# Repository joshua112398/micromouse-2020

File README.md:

# micromouse-2020

Board and schematic files for use on EAGLE or other compatible software.

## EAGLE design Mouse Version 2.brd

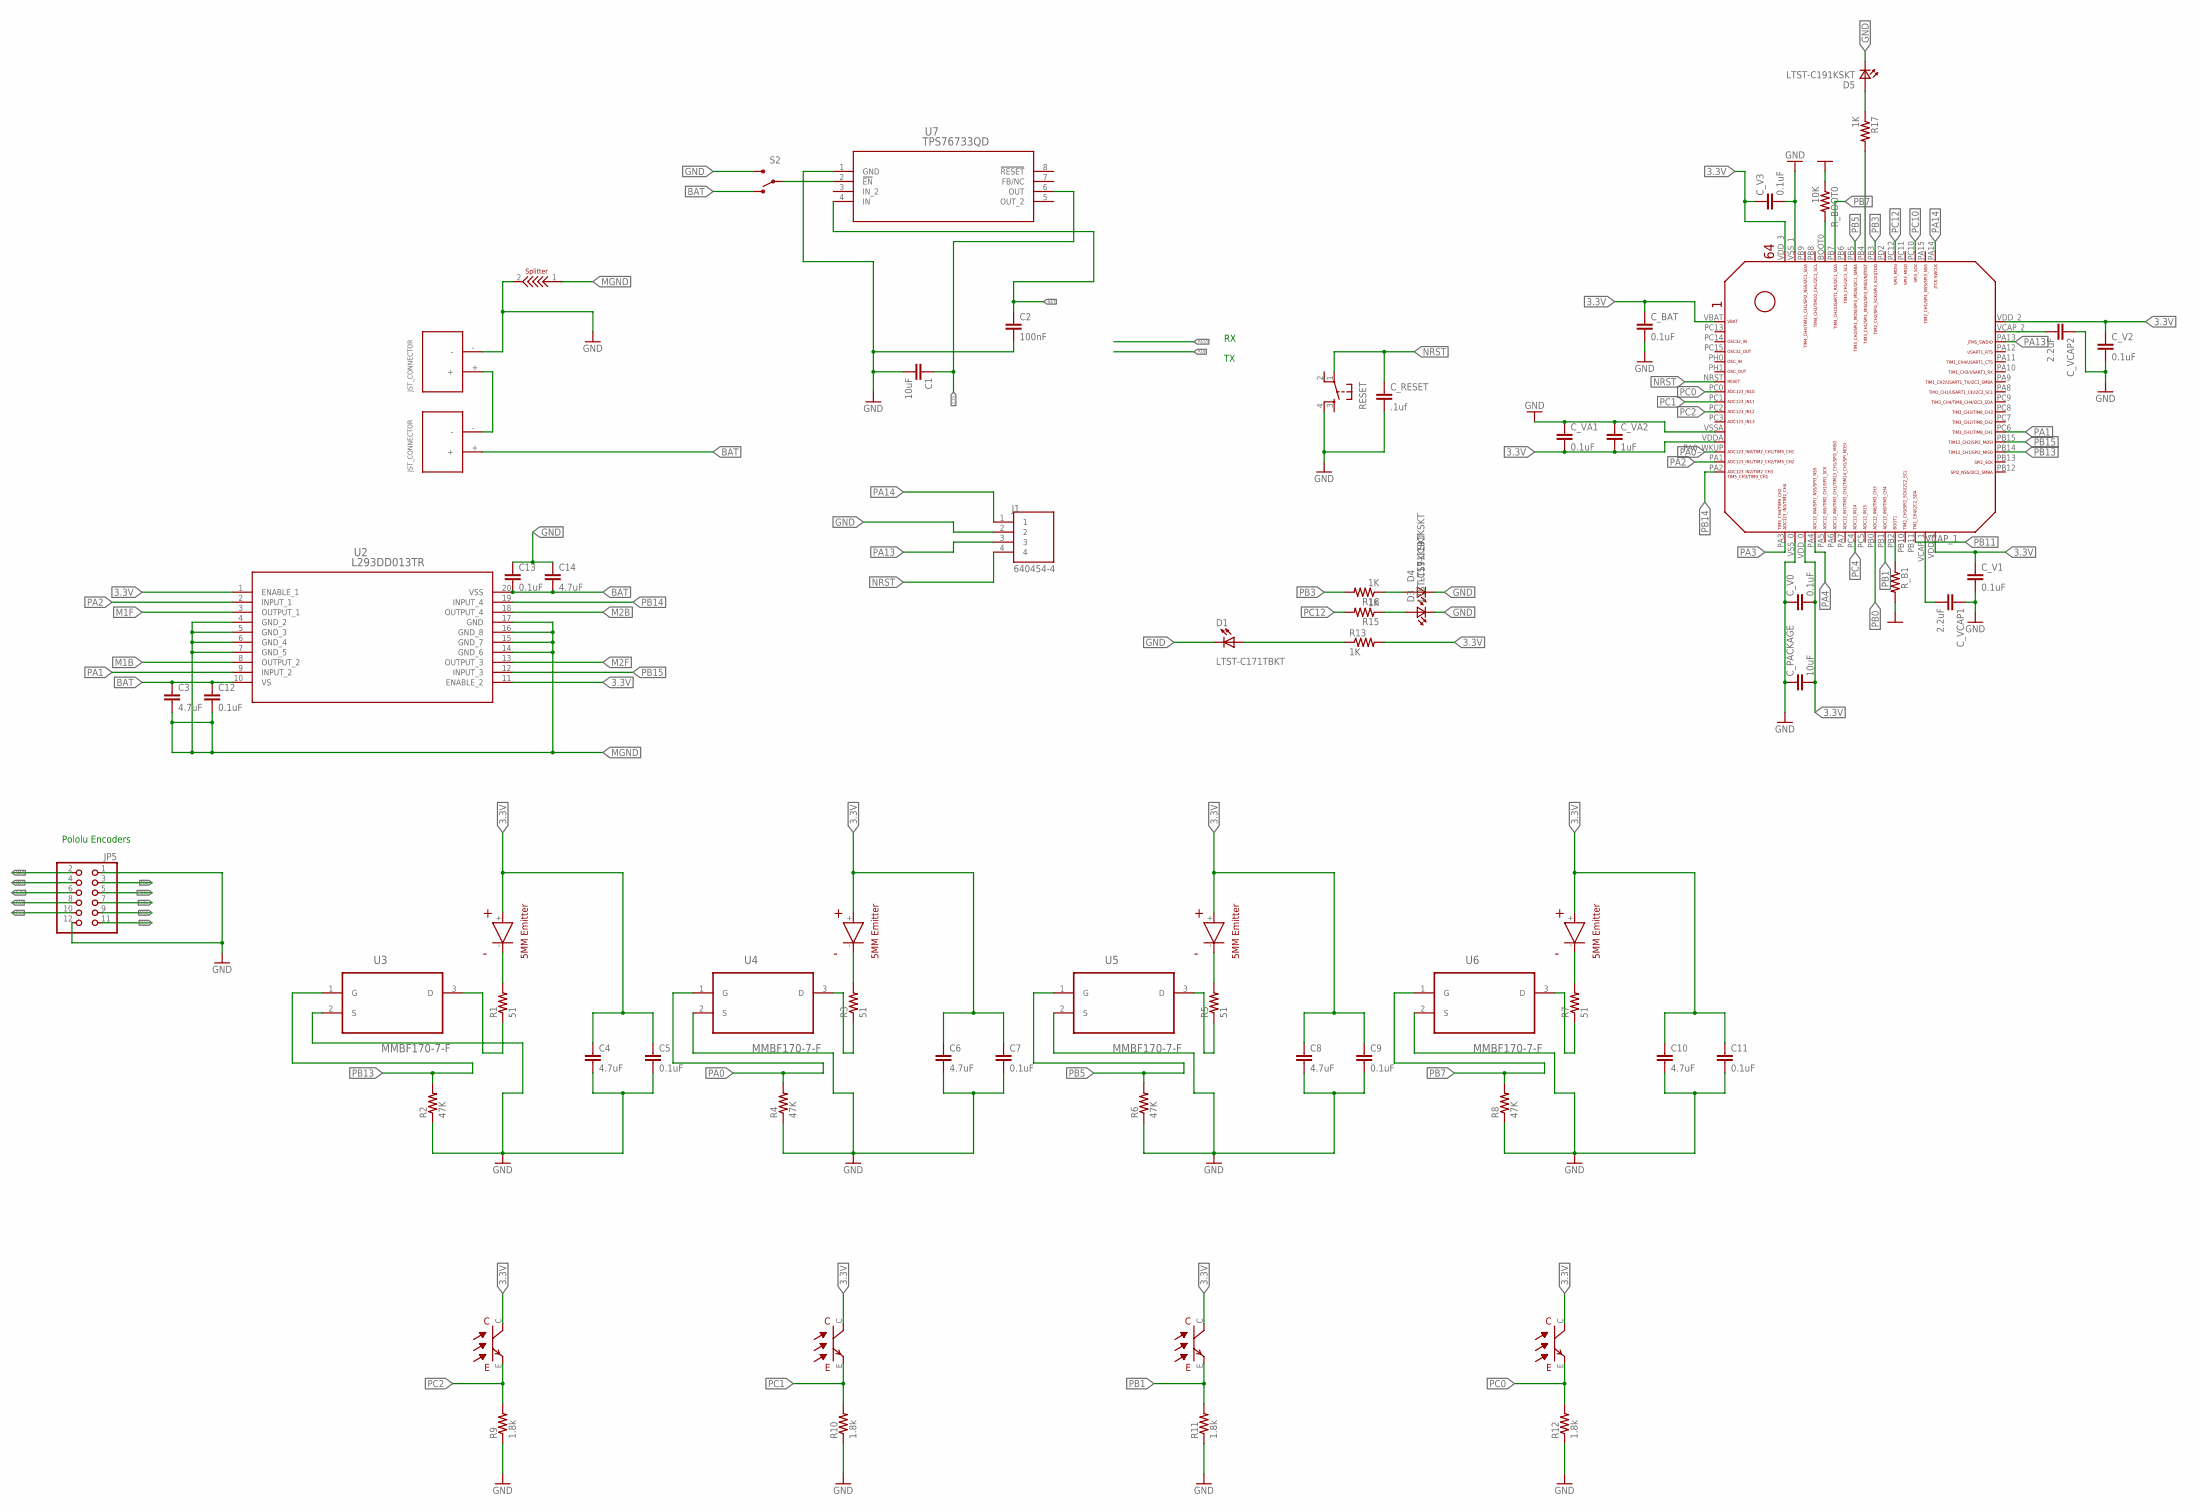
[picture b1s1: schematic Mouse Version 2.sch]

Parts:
C1: 10uF; 0603-CAP
C2: 100nF; 0603-CAP
C3, C14: 4.7uF; 0603-CAP
C4, C6, C8, C10: 4.7uF; C1206
C5, C7, C9, C11: 0.1uF; C1206
C12, C13: 0.1uF; 0603-CAP
C_BAT: 0.1uF; 0603-CAP
C_PACKAGE: 10uF; 0603-CAP
C_RESET: .1uf; 0603
C_V0, C_V1, C_V2, C_V3: 0.1uF; 0603-CAP
C_VA1: 0.1uF; 0603-CAP
C_VA2: 1uF; 0603-CAP
C_VCAP1, C_VCAP2: 2.2uF; 0603-CAP
D1: LTST-C171TBKT; DIOC200X125X110
D3, D4, D5: LTST-C191KSKT; 0603
J1: 640454-4; TE_640454-4
JP5: PINHD-2X6; 2X06
R1, R3, R5, R7: 51; R0603
R2, R4, R6, R8: 47K; R0603
R9, R10, R11, R12: 1.8k; R0603
R13, R15, R16, R17: 1K; R0603
RESET: TAC_SWITCHPTH; TACTILE-PTH
R_B1: 10K; 0603-RES
R_BOOT0: 10K; 0603-RES
S2: SWITCH-SPSTPTH; SWITCH-SPDT
U2: L293DD013TR; SO-20
U3, U4, U5, U6: MMBF170-7-F; SOT103P240X110-3N
U7: TPS76733QD; D8
U$1, U$2: JST_CONNECTOR_FEMALE
U$3: SPLITTER
U$4, U$15, U$18, U$19: RECEIVER
U$5, U$6, U$7, U$8: EMITTER
U$9: STM32F405/415_LQFP64

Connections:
3.3V: C1.1, C4.1, C5.1, C6.1, C7.1, C8.1, C9.1, C10.1, C11.1, C_BAT.1, C_PACKAGE.2, C_V0.2, C_V1.1, C_V2.1, C_V3.1, C_VA1.2, C_VA2.2, JP5.6, JP5.7, R13.2, U2.1 (ENABLE_1), U2.11 (ENABLE_2), U7.6 (OUT), U$4.C, U$5.+, U$6.+, U$7.+, U$8.+, U$9.VBAT, U$9.VDDA, U$9.VDD_0, U$9.VDD_1, U$9.VDD_2, U$9.VDD_3, U$15.C, U$18.C, U$19.C
BAT: C2.1, C3.1, C12.1, C13.2, C14.2, S2.1 (O), U2.10 (VS), U2.20 (VSS), U7.4 (IN), U$2.+
BOOT0: R_BOOT0.2, U$9.BOOT0
GND: C1.2, C2.2, C4.2, C5.2, C6.2, C7.2, C8.2, C9.2, C10.2, C11.2, C13.1, C14.1, C_BAT.2, C_PACKAGE.1, C_RESET.2, C_V0.1, C_V1.2, C_V2.2, C_V3.2, C_VA1.1, C_VA2.1, C_VCAP1.1, C_VCAP2.1, D1.-, D3.1 (K2), D4.1 (K2), D5.1 (K2), J1.2, JP5.1, JP5.12, R2.1, R4.1, R6.1, R8.1, R9.1, R10.1, R11.1, R12.1, RESET.4, R_B1.2, R_BOOT0.1, S2.3 (S), U3.2 (S), U4.2 (S), U5.2 (S), U6.2 (S), U7.1 (GND), U$1.-, U$3.2, U$9.VSSA, U$9.VSS_0, U$9.VSS_1
M1B: JP5.9, U2.8 (OUTPUT_2)
M1F: JP5.11, U2.3 (OUTPUT_1)
M2B: JP5.2, U2.18 (OUTPUT_4)
M2F: JP5.4, U2.13 (OUTPUT_3)
MGND: C3.2, C12.2, U2.4 (GND_2), U2.5 (GND_3), U2.6 (GND_4), U2.7 (GND_5), U2.14 (GND_6), U2.15 (GND_7), U2.16 (GND_8), U2.17 (GND), U$3.1
unnamed: U$1.+, U$2.-
unnamed: R3.2, U$6.-
unnamed: S2.2, U7.2 (!EN)
unnamed: C_VCAP2.2, U$9.VCAP_2
unnamed: R1.2, U$5.-
unnamed: R1.1, U3.3 (D)
unnamed: D1.+, R13.1
unnamed: R3.1, U4.3 (D)
unnamed: R5.2, U$7.-
unnamed: R5.1, U5.3 (D)
unnamed: R7.2, U$8.-
unnamed: R7.1, U6.3 (D)
unnamed: D3.2 (A2), R15.1
unnamed: D4.2 (A2), R16.1
unnamed: D5.2 (A2), R17.1
NRST: C_RESET.1, J1.4, RESET.1, U$9.NRST
PA0: R4.2, U4.1 (G), U$9.PA0_WKUP (PA0_AKUP)
PA1: U2.9 (INPUT_2), U$9.PC6
PA2: U2.2 (INPUT_1), U$9.PA1
PA3: JP5.8, U$9.PA3
PA4: U$9.PA4
PA13: J1.3, U$9.PA13
PA14: J1.1, U$9.PA14
PB0: JP5.3, U$9.PB0
PB1: R11.2, U$9.PB1, U$15.E
PB2: R_B1.1, U$9.PB2
PB3: R16.2, U$9.PB3
PB4: R17.2, U$9.PB4
PB5: R6.2, U5.1 (G), U$9.PB5
PB7: R8.2, U6.1 (G), U$9.PB7
PB11: JP5.5, U$9.PB11
PB13: R2.2, U3.1 (G), U$9.PB14
PB14: U2.19 (INPUT_4), U$9.PA2
PB15: U2.12 (INPUT_3), U$9.PB15
PC0: R12.2, U$4.E, U$9.PC0
PC1: R10.2, U$9.PC1, U$18.E
PC2: R9.2, U$9.PC2, U$19.E
PC4: JP5.10, U$9.PC4
PC10: U$9.PC10
PC12: R15.2, U$9.PC12
VCAP_1: C_VCAP1.2, U$9.VCAP_1

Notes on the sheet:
Pololu Encoders

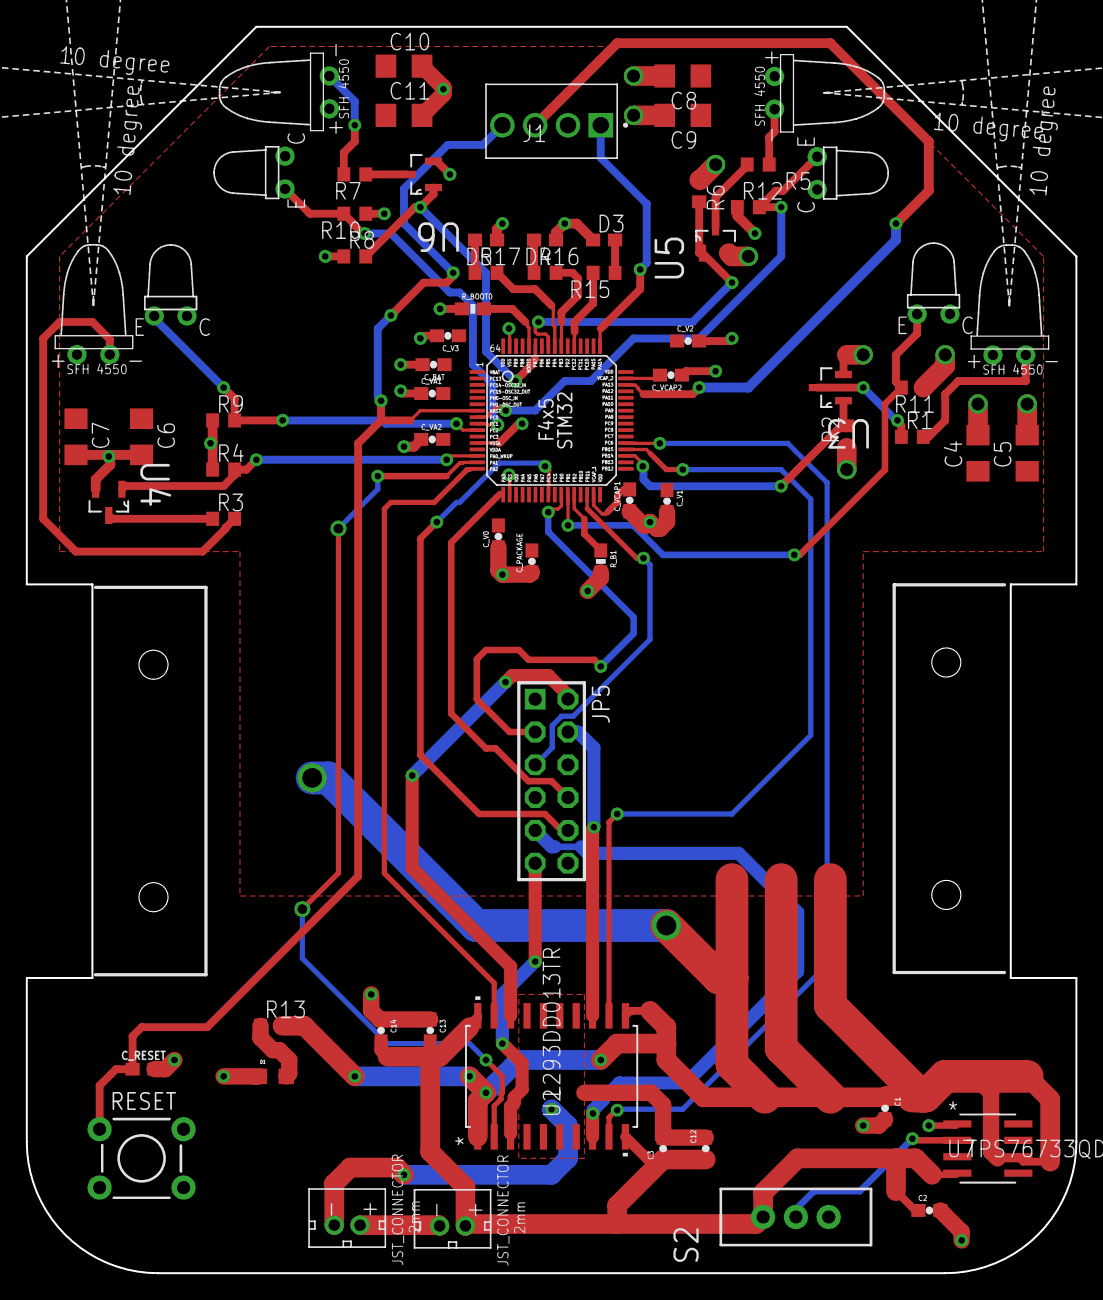
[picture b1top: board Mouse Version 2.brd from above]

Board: 2 copper layers, 81.3 x 96.5 mm, 69 parts (0 on the bottom side), 48 nets.

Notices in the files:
parts and their libraries:
SparkFun: Licensing: CC v3.0 Share-Alike You are welcome to use this library for commercial purposes.
SparkFun-Capacitors: Licensing: Creative Commons ShareAlike 4.0 International - https://creativecommons.org/licenses/by-sa/4.0
